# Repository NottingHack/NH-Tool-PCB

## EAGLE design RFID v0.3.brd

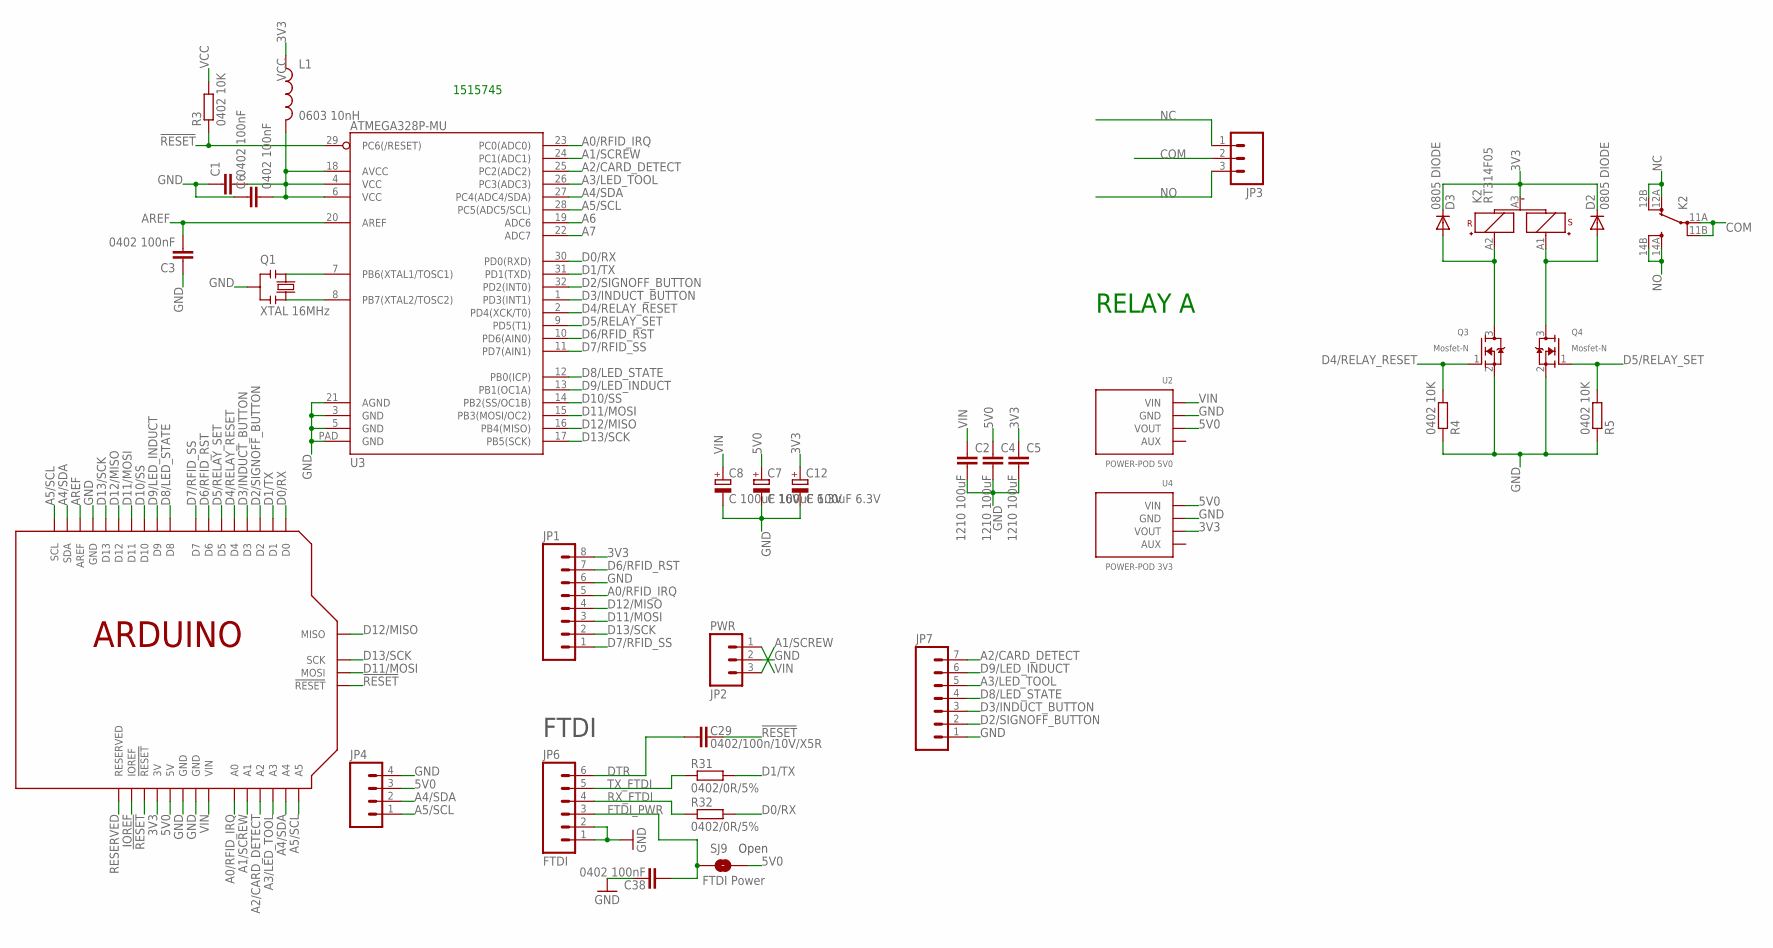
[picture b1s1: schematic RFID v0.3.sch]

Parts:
C1, C3, C6, C38: 0402 100nF; C0402-SMALLER
C2, C4, C5: 1210 100uF; C1210
C7, C12: C 100uF 6.3V; PANASONIC_C
C8: C 100uF 16V; PANASONIC_C
C29: 0402/100n/10V/X5R; C0402-ARDUINO-ROUND
D2, D3: 0805 DIODE; 0805-DIODE
JP1: M081X08; 1X08
JP2: PWR; SCREWTERMINAL-5MM-3
JP3: M03-SCREW-5MM; SCREWTERMINAL-5MM-3
JP4: M04PTH; 1X04
JP6: FTDI; 1X06
JP7: M07; 1X07
K2: RT314F05; RT1-BI
L1: 0603 10nH; C0603K-SMALL
Q1: XTAL 16MHz; RESONATOR
Q3, Q4: Mosfet-N; SOT23-3
R3, R4, R5: 0402 10K; R0402-SMALLER
R31, R32: 0402/0R/5%; R0402-ARDUINO-ROUND
SJ9: FTDI Power; SJ_2S-NO
U1: ARDUINOSPI-REFRENCE; ARDUINOR3-LWKTXT-REF-SPI
U2: POWER-POD 5V0; POWER-POD-LANDING
U3: ATMEGA328P-MU; MLF32-SHORT-CREAM
U4: POWER-POD 3V3; POWER-POD-LANDING

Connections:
3V3: C5.1, C12.+, D2.C, D3.C, JP1.8, K2.A3 (-), L1.1, U1.3V, U4.3 (VOUT)
5V0: C4.1, C7.+, JP4.3, SJ9.2, U1.5V, U1.5V@ISP (5V), U2.3 (VOUT), U4.1 (VIN)
!RESET: C29.1, R3.1, U1.!RESET, U1.!RESET@ISP (!RESET), U3.29 (PC6(/RESET))
A0/RFID_IRQ: JP1.5, U1.A0, U3.23 (PC0(ADC0))
A1/SCREW: JP2.3, U1.A1, U3.24 (PC1(ADC1))
A2/CARD_DETECT: JP7.7, U1.A2, U3.25 (PC2(ADC2))
A3/LED_TOOL: JP7.5, U1.A3, U3.26 (PC3(ADC3))
A4/SDA: JP4.2, U1.A4, U1.SDA, U3.27 (PC4(ADC4/SDA))
A5/SCL: JP4.1, U1.A5, U1.SCL, U3.28 (PC5(ADC5/SCL))
A6: U3.19 (ADC6)
A7: U3.22 (ADC7)
AREF: C3.2, U1.AREF, U3.20 (AREF)
COM: JP3.2, K2.11A (PA), K2.11B (PB)
D0/RX: R32.2, U1.D0, U3.30 (PD0(RXD))
D1/TX: R31.2, U1.D1, U3.31 (PD1(TXD))
D2/SIGNOFF_BUTTON: JP7.2, U1.D2, U3.32 (PD2(INT0))
D3/INDUCT_BUTTON: JP7.3, U1.D3, U3.1 (PD3(INT1))
D4/RELAY_RESET: Q3.1 (G), R4.2, U1.D4, U3.2 (PD4(XCK/T0))
D5/RELAY_SET: Q4.1 (G), R5.2, U1.D5, U3.9 (PD5(T1))
D6/RFID_RST: JP1.7, U1.D6, U3.10 (PD6(AIN0))
D7/RFID_SS: JP1.1, U1.D7, U3.11 (PD7(AIN1))
D8/LED_STATE: JP7.4, U1.D8, U3.12 (PB0(ICP))
D9/LED_INDUCT: JP7.6, U1.D9, U3.13 (PB1(OC1A))
D10/SS: U1.D10, U3.14 (PB2(SS/OC1B))
D11/MOSI: JP1.3, U1.D11, U1.MOSI, U3.15 (PB3(MOSI/OC2))
D12/MISO: JP1.4, U1.D12, U1.MISO, U3.16 (PB4(MISO))
D13/SCK: JP1.2, U1.D13, U1.SCK, U3.17 (PB5(SCK))
DTR: C29.2, JP6.6
FTDI_PWR: C38.2, JP6.3, SJ9.1
GND: C1.1, C2.2, C3.1, C4.2, C5.2, C6.1, C7.-, C8.-, C12.-, C38.1, JP1.6, JP2.2, JP4.4, JP6.1, JP6.2, JP7.1, Q1.2, Q3.2 (S), Q4.2 (S), R4.1, R5.1, U1.GND@1 (GND), U1.GND@2 (GND), U1.GND@3 (GND), U1.GND@ISP (GND), U2.2 (GND), U3.3 (GND), U3.5 (GND), U3.21 (AGND), U3.PAD (GND), U4.2 (GND)
IOREF: U1.IOREF
unnamed: D2.A, K2.A1 (S+), Q4.3 (D)
unnamed: D3.A, K2.A2 (R+), Q3.3 (D)
unnamed: Q1.1, U3.7 (PB6(XTAL1/TOSC1))
unnamed: Q1.3, U3.8 (PB7(XTAL2/TOSC2))
NC: JP3.1, K2.12A (OA), K2.12B (OB)
NO: JP3.3, K2.14A (SA), K2.14B (SB)
RESERVED: U1.RESERVED
RX_FTDI: JP6.4, R32.1
TX_FTDI: JP6.5, R31.1
VCC: C1.2, C6.2, L1.2, R3.2, U3.4 (VCC), U3.6 (VCC), U3.18 (AVCC)
VIN: C2.1, C8.+, JP2.1, U1.VIN, U2.1 (VIN)

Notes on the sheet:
FTDI
Open
RELAY A
1515745

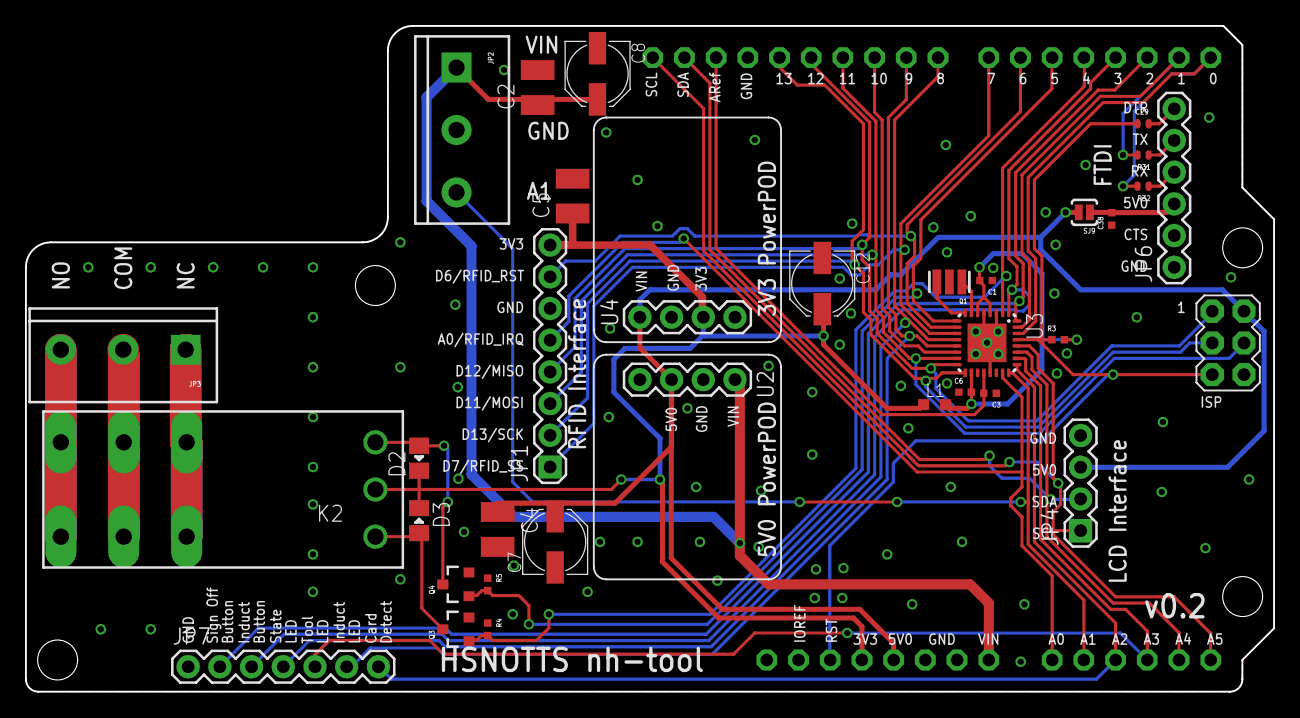
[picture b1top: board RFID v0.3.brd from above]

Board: 2 copper layers, 100.0 x 53.3 mm, 34 parts (0 on the bottom side), 38 nets.

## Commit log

2014-10-08 First push of the PCB
2016-08-17 Add early box design and some WIP board layout
2016-08-21 add laser paths and 3D models for version 2 of the RFID box
2023-05-25 missing v0.2 eagle files
2023-05-25 v0.3 wip pcb files cant remember the changes
2024-08-26 Added a PCB to avoid messy wiring
2024-08-26 Add model for Omron B3F buttons
2024-09-11 Buttons and spacers
2024-12-14 Add alternative box face for heaters 'tap for heating'

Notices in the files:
parts and their libraries:
SparkFunJan12: Licensing: CC v3.0 Share-Alike You are welcome to use this library for commercial purposes.
